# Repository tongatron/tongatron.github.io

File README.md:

# tongatron 🧪

> small repo, big rabbit hole

---

## 🌐 enter the system

👉 https://tongatron.org

Indice completo dei progetti: https://tongatron.org/projects/

---

## 🧠 what is this?

Questo repository è solo la porta d'ingresso (`tongatron.github.io`, servito su `tongatron.org`).

Dietro la porta:
- ⚙️ tools e utility web
- 🧪 esperimenti interattivi
- 🛰 prototipi IoT e hardware
- 📡 servizi self-hosted (Raspberry Pi + Cloudflare Tunnel)

---

## 🚀 progetti

### App e siti

| Progetto | URL | Repo |
|---|---|---|
| Astri — esplorazione del cielo notturno in 3D | https://tongatron.org/astri/ | [`astri`](https://github.com/tongatron/astri) |
| Il Ministero delle Eccezioni — romanzo satirico | https://tongatron.org/ministero-delle-eccezioni/ | [`ministero-delle-eccezioni`](https://github.com/tongatron/ministero-delle-eccezioni) |
| Ryanair Search — ricerca voli A/R con filtri | https://tongatron.org/projects/ryanair-search/ | locale |
| Head Tracking — interazioni con movimento testa | https://tongatron.org/head-tracking/ | [`head-tracking`](https://github.com/tongatron/head-tracking) |
| Gmail Stats — dashboard email | https://tongatron.org/gmail-stats/ | [`gmail-stats`](https://github.com/tongatron/gmail-stats) |
| PA Ninja — toolkit Pubblica Amministrazione | https://tongatron.org/pa-ninja/landing/ | [`pa-ninja`](https://github.com/tongatron/pa-ninja) |
| GTT Radar — trasporto pubblico torinese | https://gtt-to.onrender.com/ | [`gtt-to`](https://github.com/tongatron/gtt-to) |

### Pagine locali (in `/projects`)

| Progetto | URL |
|---|---|
| Moore's Law in Motion | https://tongatron.org/projects/computing-timeline/ |
| Terminale Panico Estremo | https://tongatron.org/projects/error/ |
| Password Analyzer | https://tongatron.org/projects/password-analyzer/ |
| Kinetik Laboratories | https://tongatron.org/projects/kinetiklaboratories/ |
| Partito | https://tongatron.org/projects/partito/ |
| Animations | https://tongatron.org/projects/animations/ |
| Farmaci | https://tongatron.org/projects/farmaci/ |

### IoT e installazioni

| Progetto | URL |
|---|---|
| Robottino | https://tongatron.org/projects/robottino/robottino-site/ |
| Selfomatic | https://tongatron.org/projects/selfomatic/ |
| IKEA Hack Nordli | https://tongatron.org/projects/IKEA-hack/ |
| Magazzinoweb (archivio) | https://tongatron.org/projects/magazzinoweb/ |

### Giochi e utility

Tutti sotto [`games-utilities`](https://github.com/tongatron/games-utilities):

- [Anagrammatron](https://tongatron.org/games-utilities/anagrammatron/) — generatore di anagrammi
- [Anonymous Pics](https://tongatron.org/games-utilities/anonymous-pics/) — utility fotocamera
- [Dado](https://tongatron.org/games-utilities/dado/) — simulatore di dado
- [Connect Four](https://tongatron.org/games-utilities/forza4/) — Forza Quattro vs CPU
- [Memory](https://tongatron.org/games-utilities/memory/) — memory game
- [Simulatore Morse](https://tongatron.org/games-utilities/morse/) — telegrafo + audio
- [Multi Web Simulator](https://tongatron.org/games-utilities/multi-simulator/) — simulatore MULTI
- [QR Scanner Mobile](https://tongatron.org/games-utilities/qrscanner/) — scanner QR
- [Roulette](https://tongatron.org/games-utilities/roulette/) — roulette casino-style
- [Rumore Bianco](https://tongatron.org/games-utilities/rumorebianco/) — generatore audio
- [Simon Simulator](https://tongatron.org/games-utilities/simon/) — Simon classico

### Servizi self-hosted (Raspberry Pi + Cloudflare Tunnel)

| Servizio | URL | Note |
|---|---|---|
| Raspi Chat | https://chat.tongatron.org/ | chat self-hosted con stanze |
| Magazzino Sereno | https://mhz.tongatron.org/ | catalogo personale |
| Liberia | https://library.tongatron.org/ | scanner ISBN |
| Alcol Monitor | https://alcol-monitor.tongatron.org/ | tracker personale |

Inventario completo dei servizi sul Pi: [`README.raspberry.md`](README.raspberry.md).

---

## 📊 analytics

Tutte le pagine sotto `tongatron.org` (e i servizi sul Pi via tunnel) caricano `https://tongatron.org/analytics.js` — sorgente unica, Google Analytics 4 con Consent Mode v2 e banner opt-in. Per aggiungere tracking a una nuova pagina:

```html
<script async src="https://tongatron.org/analytics.js"></script>
```

---

## 🧩 philosophy

- 🏃 build fast
- 🔁 iterate faster
- 🧱 ship real things
- 🪶 keep it lightweight
- 🧑‍🔧 break → fix → repeat

---

## 🛠 stack (more or less)

```
html · css · javascript · node · vite · fastify · express
+ whatever gets the job done
```

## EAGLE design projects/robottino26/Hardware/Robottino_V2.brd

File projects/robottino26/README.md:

# ROBOTTINO - testa rotante interattiva

Repository del progetto Robottino (hardware, design e libreria Arduino).

## Contenuti
- `Software/Robottino-ArduinoLibrary`: libreria Arduino + esempi `.ino`
- `Hardware`: schemi e board PCB (`.sch`, `.brd`, `.pdf`)
- `Design`: file `.dxf` del case
- `Education`: materiali didattici

## Avvio rapido (software)
Consulta la guida completa in `Software/Robottino-ArduinoLibrary/README.md`.

## Licenza
[Creative Commons: Attribution-ShareAlike 4.0 International](http://creativecommons.org/licenses/by-sa/4.0/)

powered by [Tongatron](http://tongatron.it/)  
hosted and developed in [Fablab Torino](http://fablabtorino.org/)

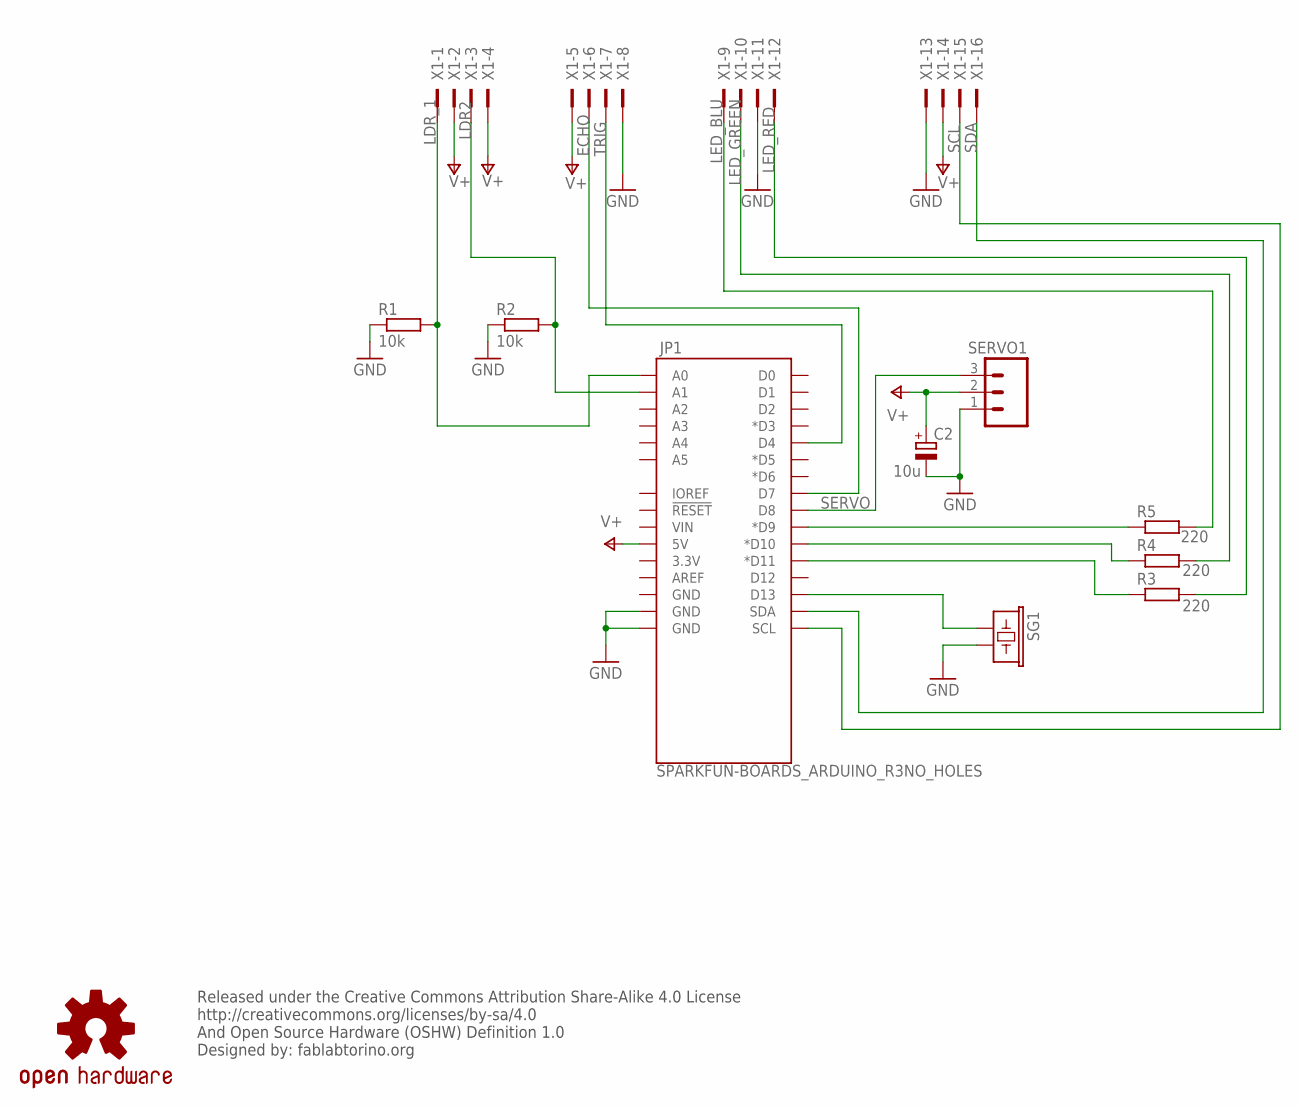
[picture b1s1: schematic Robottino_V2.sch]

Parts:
C2: 10u; E2,5-6
JP1: SPARKFUN-BOARDS_ARDUINO_R3NO_HOLES; SPARKFUN-BOARDS_ARDUINO_R3_NO_HOLES
LOGO1: OSHW-LOGOS; OSHW-LOGO-S
R1, R2: 10k; 0309/10
R3, R4, R5: 220; 0309/10
SERVO1: M03POLAR; MOLEX-1X3
SG1: SPARKFUN-ELECTROMECHANICAL_BUZZERPTH-NS-KIT; SPARKFUN-ELECTROMECHANICAL_BUZZER-12MM-NS-KIT
X1: 2516-; PAK100/2500-16

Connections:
BUZZER: JP1.D13, SG1.+ (1)
ECHO: JP1.D4, X1.7
GND: C2.-, JP1.GND@1 (GND), JP1.GND@2 (GND), R1.1, R2.1, SERVO1.1, SG1.- (2), X1.8, X1.11, X1.13
LDR2: JP1.A1, R2.2, X1.3
LDR_1: JP1.A0, R1.2, X1.1
LED_BLU: R5.2, X1.9
LED_GREEN: R4.2, X1.10
LED_RED: R3.2, X1.12
unnamed: JP1.D9 (*D9), R5.1
unnamed: JP1.D10 (*D10), R4.1
R: JP1.D11 (*D11), R3.1
SCL: JP1.SCL, X1.15
SDA: JP1.SDA, X1.16
SERVO: JP1.D8, SERVO1.3
TRIG: JP1.D7, X1.6
V+: C2.+, JP1.5V, SERVO1.2, X1.2, X1.4, X1.5, X1.14

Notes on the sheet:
Released under the Creative Commons Attribution Share-Alike 4.0 License http://creativecommons.org/licenses/by-sa/4.0 And Open Source Hardware (OSHW) Definition 1.0 Designed by: fablabtorino.org

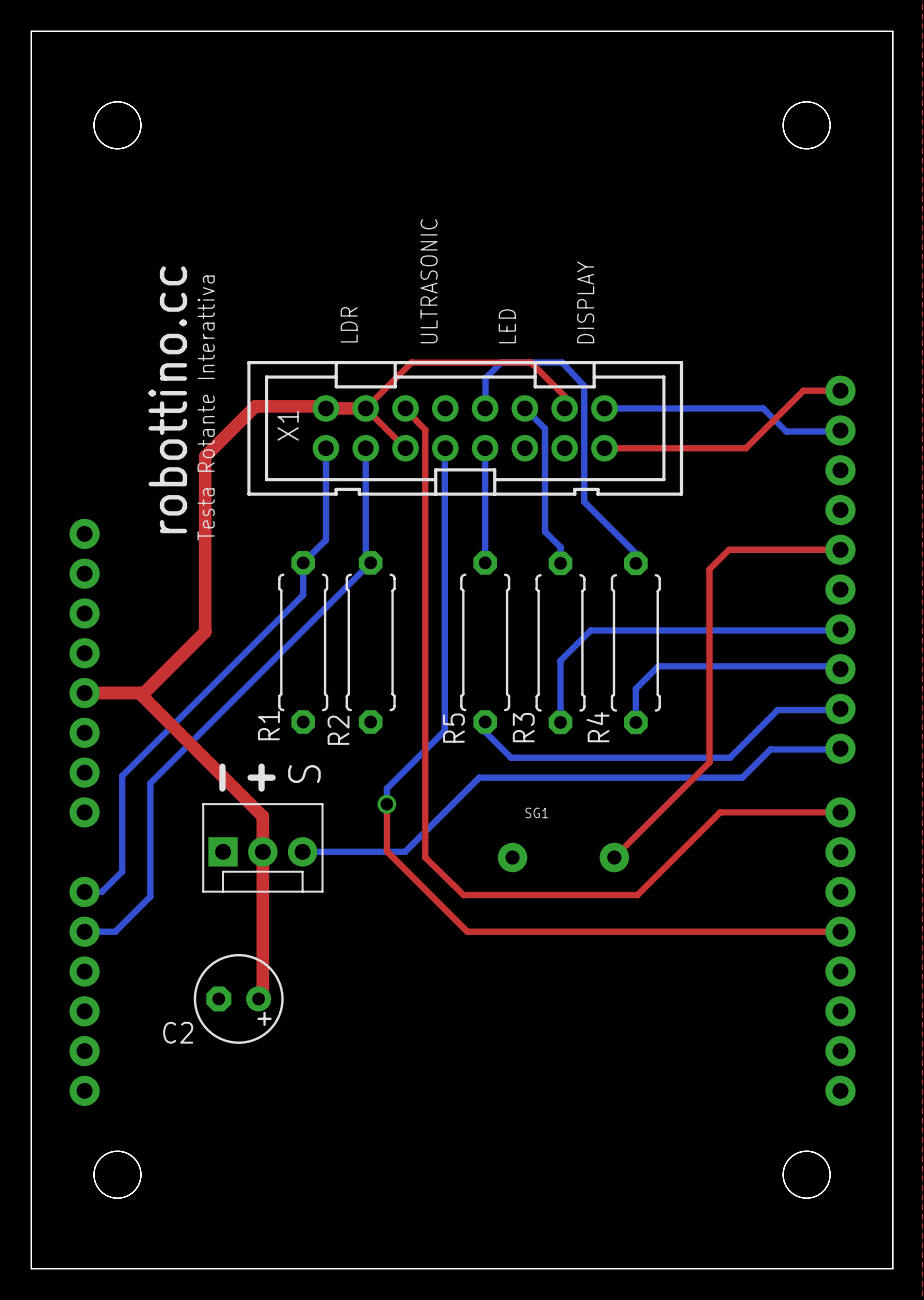
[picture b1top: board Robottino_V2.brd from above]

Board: 2 copper layers, 55.0 x 79.0 mm, 11 parts (0 on the bottom side), 16 nets.

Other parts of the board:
E$1: OSHW-LOGO-S_COPPER

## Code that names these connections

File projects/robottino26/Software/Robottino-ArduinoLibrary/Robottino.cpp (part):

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#define RED_PIN 11
#define GRN_PIN 10
#define BLU_PIN 9
#define SERVO_PIN 8
#define TRIG_PIN 7
#define ECHO_PIN 4
#define LDR_DX_PIN A0
#define LDR_SX_PIN A1

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void sensorsInit() {
  pinMode(LDR_DX_PIN, INPUT);
  pinMode(LDR_SX_PIN, INPUT);
  pinMode(TRIG_PIN, OUTPUT);
  pinMode(ECHO_PIN, INPUT);
}


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// Returns distance in cm
int Robottino::leggiDistanza () {               //can't use newPing library because of compatibility problems with tone() on Arduino UNO
  if (millis() - previousSonicMillis > 50) {
    digitalWrite(TRIG_PIN, HIGH);   //(see: http://forum.arduino.cc/index.php?topic=184162.0 )
    delay(1);
    digitalWrite(TRIG_PIN, LOW);
    int distance = pulseIn(ECHO_PIN, HIGH, 5700) / 57;  //Timeout if distance > 100 cm; divide by round-trip microseconds per cm to get cm
    distanzaRilevata = distance;
    previousSonicMillis = millis();
  }
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  //// multiply frequency, which is really cycles per second, by the number of seconds to
  //// get the total number of cycles to produce
  for (long i=0; i < numCycles; i++){ // for the calculated length of time...
    digitalWrite(BUZZ_PIN,HIGH); // write the buzzer pin high to push out the diaphram
    delayMicroseconds(delayValue); // wait for the calculated delay value
    digitalWrite(BUZZ_PIN,LOW); // write the buzzer pin low to pull back the diaphram
    delayMicroseconds(delayValue); // wait again or the calculated delay value
  }
  //digitalWrite(BLU_PIN,LOW);
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unsigned long previousServoMillis = 0;

void servoInit () {
  servo.attach(SERVO_PIN);
  servo.write(90);
  SoftwareServo::refresh();
  delay(30);    // wait for the servo to reach that position
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
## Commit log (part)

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2026-03-17 chore(ps-torino): update live snapshot
2026-03-18 panel
2026-03-18 ordine
2026-03-18 PS json
2026-03-18 deploy PS
2026-03-18 simple PS
2026-03-18 PS 3
2026-03-18 index no filtri PS
2026-03-18 font
2026-03-18 update PS
2026-03-19 PSultimo snapshot
2026-03-19 PS push
2026-03-19 push PS
2026-03-19 via italia simulator
2026-03-19 via italia 2
2026-03-19 no via Italia
2026-03-19 sitemap
2026-03-19 via biella
2026-03-19 via ITalia
2026-03-19 PS update e via Italia
2026-03-19 UI PS
2026-03-19 via ITaia mobile
2026-03-19 style PS
2026-03-19 magnino
2026-03-19 frecce
2026-03-19 PS scope
2026-03-19 PS scraping
2026-03-19 links
2026-03-19 freccia
2026-03-19 moretti
2026-03-19 moretti per preview
2026-03-19 Fix moretti static deploy assets
2026-03-19 Ignore moretti dependencies
2026-03-19 Moretti2
2026-03-19 Add editable Moretti edition
2026-03-19 admin
2026-03-19 Remove duplicate Moretti path casing
2026-03-19 editable
2026-03-19 update test
2026-03-20 riviera
2026-03-20 siemap
2026-03-20 kinetic
2026-03-20 controlli
2026-03-20 barra
2026-03-20 link
2026-03-21 starrynight
2026-03-21 paanel
2026-03-21 fix render bind
2026-03-21 lighten render gtfs loading
2026-03-21 fix quoted shapes parsing
2026-03-21 many
2026-03-22 file
2026-03-23 assemblea
2026-03-23 index
2026-03-23 nomi
2026-03-24 ass2
2026-03-24 build a metà
2026-03-26 macosdashboard
2026-03-26 pulizia
2026-03-27 pics
2026-03-27 pixel
2026-03-27 pixels
2026-03-27 pixel PWA
2026-03-27 pixel share
2026-03-27 pixel barra nera
2026-03-27 pixels 3
2026-03-27 pixel x
2026-03-27 nuova foto
2026-03-27 anon TWA
2026-03-27 Remove TWA setup and keep PWA only
2026-03-28 projects in Jekill
2026-03-28 pubblico test
2026-03-31 analitycs
2026-04-01 refactor: simplify projects archive and refresh homepage
2026-04-01 style: compact homepage featured project cards
2026-04-01 fix: rename Osservatorio Delmastro
2026-04-04 refactor: rebalance project cards and remove Delmastro
2026-04-05 feat: add minimal markdown builder for projects
2026-04-11 canvas
2026-04-12 feat: add Raspi Chat to featured projects
2026-04-12 feat: add project cover images to homepage
2026-04-12 chore: align project cover images
2026-04-12 new img
2026-04-13 Add contact form test page
2026-04-16 Add PA Ninja to featured projects
2026-04-17 Revise README for clarity and new structure
    Updated the README to reflect a new minimalistic approach and added sections for philosophy and contact.
2026-04-17 Revise README structure and content
    Updated README to enhance clarity and organization.
2026-04-17 index meglio
2026-04-17 Refine project action buttons
2026-04-17 Adjust project archive card styling
2026-04-17 Refine project card presentation
2026-04-17 Add games section to homepage
2026-04-17 Update homepage project sections
2026-04-17 Polish homepage layout details
2026-04-17 metda
2026-04-17 title
2026-04-18 dado
2026-04-18 Remove games and simulators section from homepage
2026-04-18 Remove Jekyll stack and panel assets
2026-04-21 Tune balloon dust effect
2026-04-26 Add Gmail Stats card to recent projects on index
2026-04-26 Add Tongatron site icons
2026-04-26 Replace homepage headline with portrait
2026-04-26 Reduce homepage portrait size
2026-04-26 Remove homepage portrait border
2026-04-28 passoword
2026-04-28 password leaks versione
2026-04-28 office password an
2026-04-28 error
2026-04-29 Update site contact flow and project pages
2026-04-30 Update README.raspberry.md: raspi-admin + raspi2 nodes
2026-04-30 login
2026-05-02 computing-timeline
2026-05-02 how long
2026-05-02 meta
2026-05-02 Moore's Law in Motion
2026-05-02 Aggiungi confronto benchmark: consenti selezione singola macchina dopo test
    - updateBar(): abilita Compare quando benchmark è eseguito e n >= 1 (prima richiedeva n >= 2)
    - openModal(): accetta 1 macchina se benchmark è stato eseguito
    - Aggiunge 'This Computer' come prima colonna nella tabella di confronto
    - Mostra tempo misurato in giallo per il benchmark
    - Calcola e mostra tempi stimati per macchine storiche
    - Filtra valori -1 nel calcolo delle scale logaritmiche
2026-05-02 Risolvi bug: abilita Compare button dopo benchmark
    Il callback del benchmark completato non chiamava updateBar(), quindi
    il Compare button rimaneva disabilitato anche con 1+ macchine selezionate.
    Ora updateBar() viene chiamato dopo che lastBenchmarkResult viene impostato.
2026-05-02 Correggi benchmark comparison: reset su clear selection e migliora formattazione
    - Azzera lastBenchmarkResult quando si clicca 'Clear selection' per reset corretto della logica Compare button
    - Migliora formattazione della comparison con spaziatura migliore tra le voci
    - Risolve bug dove Compare button rimane abilitato con benchmark dopo clear selection
2026-05-02 Correggi bug comparison senza benchmark: controlla lastBenchmarkResult prima di accedere a .ops
2026-05-02 Correggi calcolo ratio benchmark: inverte formula per mostrare correttamente il confronto
2026-05-02 Correggi formattazione formatMips: mostra GIPS/MIPS invece di 'billion IPS'
2026-05-02 Correggi MIPS database: Xiaomi Redmi 12 da 35k a 210k MIPS (MediaTek Helio G88)
2026-05-05 variazioni
2026-05-05 Add V6 homepage design refinements
2026-05-05 Refine V6 IoT layout and hero image
2026-05-05 Tighten V6 IoT intro block
2026-05-05 Increase V6 Fablab logo size
2026-05-05 Add homepage design variants and asset updates
2026-05-05 Add homepage V2
2026-05-05 Refine homepage V2 layout
2026-05-05 Polish homepage metadata and favicon
2026-05-05 Update header and add Titillium font variant
2026-05-05 new index
2026-05-05 projets
2026-05-05 Add hidden link on Tongatron in footer to projects page
2026-05-06 Fix home page title
2026-05-10 prova
2026-05-10 digital
2026-05-14 Add Partito markdown viewer project
2026-05-14 Expand Partito political analysis
2026-05-14 Show Partito publication timestamp
2026-05-14 Advance Partito chronology and program
2026-05-14 Add Partito audience matrix
2026-05-14 Add Partito party comparison
2026-05-14 Add Partito brief manifesto
2026-05-14 Update partito reader and add epub download
2026-05-14 Add Tongatron project links to projects index
2026-05-15 Add PayPal components to pulsanti page
2026-05-20 Redesign availability banner
2026-05-20 Refine availability banner styling
2026-05-20 Center and recolor availability banner
2026-05-20 Lighten availability banner palette
2026-05-20 Update availability banner copy
2026-05-20 Remove availability banner hover effects
2026-05-20 Add shared analytics opt-out across tongatron subdomains
2026-05-20 Keep availability banner text readable on hover
2026-05-22 Add AI-focused homepage variant
2026-05-22 Promote AI homepage and archive previous index
2026-05-22 Clean up SEO metadata and project URLs
2026-05-22 Improve project SEO copy for titles and descriptions
2026-05-22 Fix availability banner full-width layout
2026-05-22 Riduci ridondanze nella sezione AI
    Rimuove il blocco ai-proof che duplicava i bullet di ai-points
    (rapid prototyping, debug/refactor, integrazioni) e accorcia la lista
    puntata collegandola a progetti concreti del portfolio. Aggiorna le
    ai-side card per esplicitare lo stack tecnico (linguaggi, runtime,
    hardware) e rendere la sezione piu utile per chi valuta competenze.
    https://claude.ai/code/session_01PYXtZ9ES8peY5rX45Pr8iE
2026-05-22 Refine homepage recruiting copy
2026-05-22 Aggiungi versione con data e ora nel footer
2026-05-22 Aggiorna metadata per usare giovannibindi2.jpg
2026-05-26 Add Birth Lottery to projects section

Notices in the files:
parts and their libraries:
SparkFun-Connectors: Licensing: Creative Commons ShareAlike 4.0 International - https://creativecommons.org/licenses/by-sa/4.0
